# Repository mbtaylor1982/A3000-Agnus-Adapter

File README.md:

# A3000-Agnus-Adapter

## Intoduction
With the 8372B Agnus being a rare and expensive beast this adator was designed to allow the use of the relativly common 390544 (8375) 2MB Agnus from the A500+ and A600 in the A3000. 

## PAL or NTSC
Unlike the 8372B which can be changed between NTSC and PAL with a jumper, the 8375 (390544) can not. 

When selecting an Agnus chip to use with this adaptor there are two choices that have been tested:

1. 390544-01 PAL 2MB Agnus used in Eurpean A500+ and A600
2. 390544-02 NTSC 2MB Agnus Used in North American A500+ and A600

Other variants of the Agnus chip exist and provision has been made for then Vbb connection on pin 40 (C14M). 

If using one of the chips marked Vbb, C2 should be populated with a 0.1uF ceramic capacitor.

**Please note I have not tested any of the below chip revisions so the following info is provided as-is**

>318069-10
>Several pins have been changed to support the A600. This device supports PAL only - the PAL/_NTSC pad is internally pulled up to Vdd (+5). This part is the new rev of >what was previously called 390554-01, except that Vbb replaces the C14M pin.
>
>318069-11
>This pinout is identical to the -10. However, this device supports NTSC only - the PAL/_NTSC pad is internally connected to GND. This part is the new rev of what was >previously called 390554-02, except that Vbb replaces the C14M pin.
>
>318069-12
>Several pins have been changed to support the A600. This device supports PAL only - the PAL/_NTSC pad is internally pulled up to Vdd (+5). This part is the new rev of >what was previously called 390554-01.
>
>318069-13
>Several pins have been changed to support the A600. This device supports NTSC only - the PAL/_NTSC pad is internally connected to ground. This part is the new rev of >what was previously called 390554-02.

Source of above info > https://www.amigawiki.org/lib/exe/fetch.php?media=de:parts:agnus-history.pdf

## Components

| Component                                   | Location  | Qty | Link |
| ------------------------------------------- | --------- | --- | ---- |
| Ceramic Capacitor, 0.1uF, 0805              | C1, C2    | 2   |  [Mouser](https://www.mouser.com/ProductDetail/710-885012207098)    |
| 74AHC1G08 Single 2-Input AND Gate, SOT-23-5 | IC4       | 1   |  [Mouser](https://www.mouser.com/ProductDetail/595-SN74AHC1G08DBVR)    |
| PLCC 84 THT Socket                          |           | 1   | [Mouser](https://www.mouser.com/ProductDetail/3M-Electronic-Solutions-Division/8484-11B1-RK-TP?qs=WZRMhwwaLl9eNFJXLRGlFw==) |
|22-Pin, 2 Row Female header||4|[Mouser](https://www.mouser.se/ProductDetail/517-929975-01-11-RK)||
|22-Pin, 2 Row Male header||4|[Mouser](https://www.mouser.se/ProductDetail/649-77313-118-22LF)||

## Thanks
Thankyou to all the people who have helped with this project.

- Tristan Zondag for testing the adaptor (1st person to get it fully working)
- [Matt Harlum Liv2](https://github.com/LIV2) RAS signal combining inspired by the [A500-2Meg-Chip-ram](https://github.com/LIV2/A500-2Meg-Chip-ram) project.
- [John Chucky Hertell](https://github.com/ChuckyGang) & Peter Mulholland, initial conversations about the idea of using an A500+ Agnus.

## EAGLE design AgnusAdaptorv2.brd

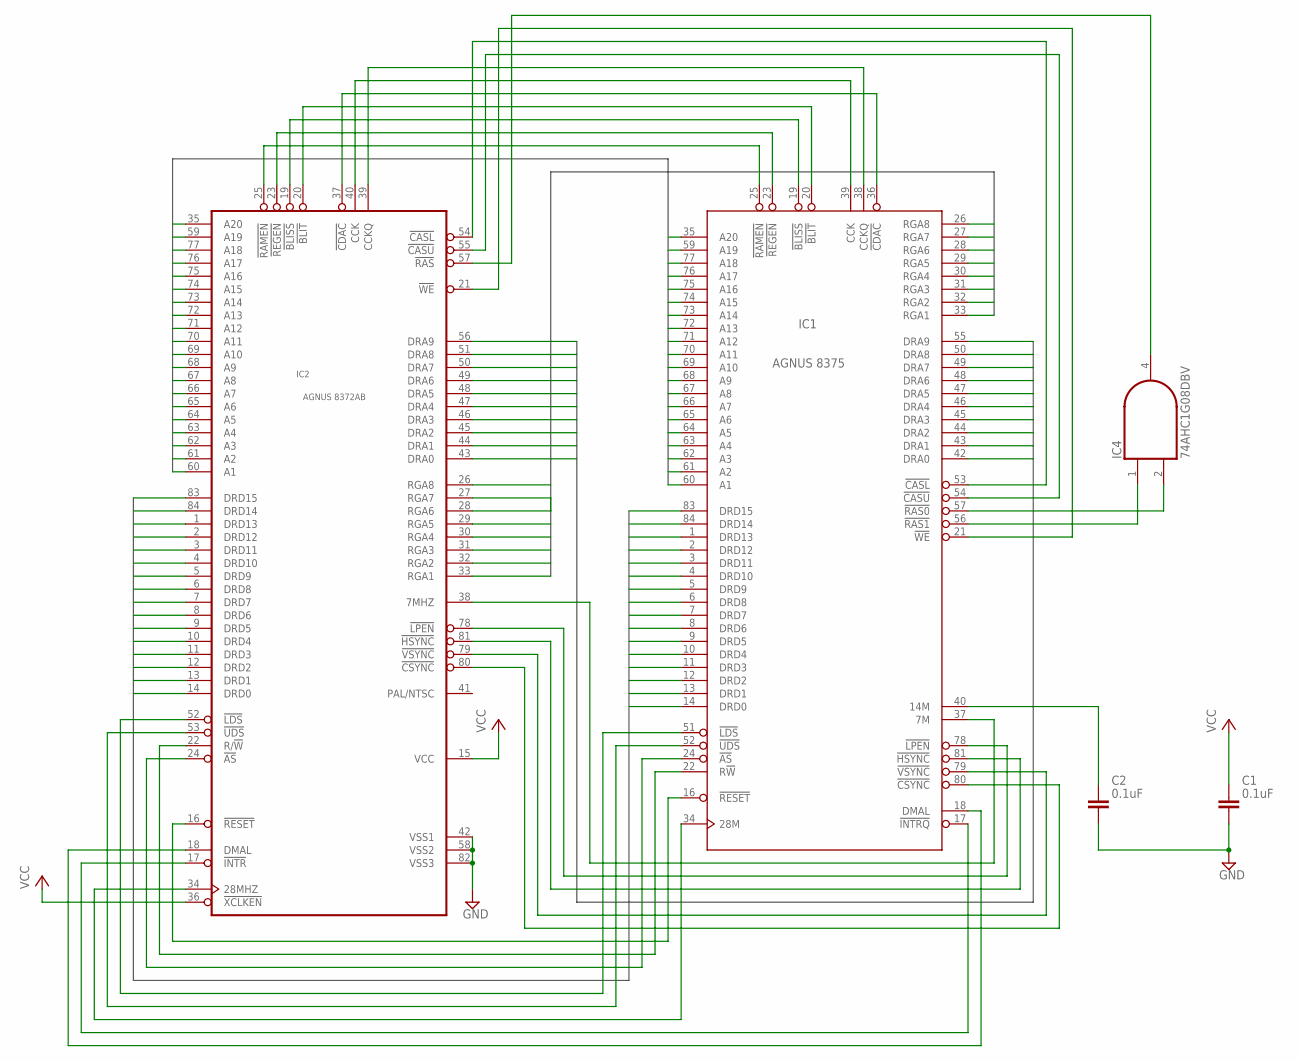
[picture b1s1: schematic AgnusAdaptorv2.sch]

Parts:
C1, C2: 0.1uF; CAPC2012X110
IC1: AGNUS_8375_A500+_A600_THT; PLCC84_T
IC2: A3000 Agnus Socket; PLCC84_T_H
IC4: 74AHC1G08DBV; SOT23-5

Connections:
7MHZ: IC1.37 (7M), IC2.38 (7MHZ)
28MHZ: IC1.34 (28M), IC2.34 (28MHZ)
!AS: IC1.24 (!AS), IC2.24 (!AS)
!BLISS: IC1.19 (!BLISS), IC2.19 (!BLISS)
!BLIT: IC1.20 (!BLIT), IC2.20 (!BLIT)
!CASL: IC1.53 (!CASL), IC2.54 (!CASL)
!CASU: IC1.54 (!CASU), IC2.55 (!CASU)
!CDAC: IC1.36 (!CDAC), IC2.37 (!CDAC)
!CSYNC: IC1.80 (!CSYNC), IC2.80 (!CSYNC)
!HSYNC: IC1.81 (!HSYNC), IC2.81 (!HSYNC)
!INTRQ: IC1.17 (!INTRQ), IC2.17 (!INTR)
!LDS: IC1.51 (!LDS), IC2.52 (!LDS)
!LPEN: IC1.78 (!LPEN), IC2.78 (!LPEN)
!RAMEN: IC1.25 (!RAMEN), IC2.25 (!RAMEN)
!RAS: IC2.57 (!RAS), IC4.4 (O)
!RAS0: IC1.57 (!RAS0), IC4.2 (I1)
!RAS1: IC1.56 (!RAS1), IC4.1 (I0)
!REGEN: IC1.23 (!REGEN), IC2.23 (!REGEN)
!RESET: IC1.16 (!RESET), IC2.16 (!RESET)
!UDS: IC1.52 (!UDS), IC2.53 (!UDS)
!VSYNC: IC1.79 (!VSYNC), IC2.79 (!VSYNC)
!WE: IC1.21 (!WE), IC2.21 (!WE)
A1: IC1.60 (A1), IC2.60 (A1)
A2: IC1.61 (A2), IC2.61 (A2)
A3: IC1.62 (A3), IC2.62 (A3)
A4: IC1.63 (A4), IC2.63 (A4)
A5: IC1.64 (A5), IC2.64 (A5)
A6: IC1.65 (A6), IC2.65 (A6)
A7: IC1.66 (A7), IC2.66 (A7)
A8: IC1.67 (A8), IC2.67 (A8)
A9: IC1.68 (A9), IC2.68 (A9)
A10: IC1.69 (A10), IC2.69 (A10)
A11: IC1.70 (A11), IC2.70 (A11)
A12: IC1.71 (A12), IC2.71 (A12)
A13: IC1.72 (A13), IC2.72 (A13)
A14: IC1.73 (A14), IC2.73 (A14)
A15: IC1.74 (A15), IC2.74 (A15)
A16: IC1.75 (A16), IC2.75 (A16)
A17: IC1.76 (A17), IC2.76 (A17)
A18: IC1.77 (A18), IC2.77 (A18)
A19: IC1.59 (A19), IC2.59 (A19)
A20: IC1.35 (A20), IC2.35 (A20)
CCK: IC1.39 (CCK), IC2.40 (CCK)
CCKQ: IC1.38 (CCKQ), IC2.39 (CCKQ)
DMAL: IC1.18 (DMAL), IC2.18 (DMAL)
DRA0: IC1.42 (DRA0), IC2.43 (DRA0)
DRA1: IC1.43 (DRA1), IC2.44 (DRA1)
DRA2: IC1.44 (DRA2), IC2.45 (DRA2)
DRA3: IC1.45 (DRA3), IC2.46 (DRA3)
DRA4: IC1.46 (DRA4), IC2.47 (DRA4)
DRA5: IC1.47 (DRA5), IC2.48 (DRA5)
DRA6: IC1.48 (DRA6), IC2.49 (DRA6)
DRA7: IC1.49 (DRA7), IC2.50 (DRA7)
DRA8: IC1.50 (DRA8), IC2.51 (DRA8)
DRA9: IC1.55 (DRA9), IC2.56 (DRA9)
DRD0: IC1.14 (DRD0), IC2.14 (DRD0)
DRD1: IC1.13 (DRD1), IC2.13 (DRD1)
DRD2: IC1.12 (DRD2), IC2.12 (DRD2)
DRD3: IC1.11 (DRD3), IC2.11 (DRD3)
DRD4: IC1.10 (DRD4), IC2.10 (DRD4)
DRD5: IC1.9 (DRD5), IC2.9 (DRD5)
DRD6: IC1.8 (DRD6), IC2.8 (DRD6)
DRD7: IC1.7 (DRD7), IC2.7 (DRD7)
DRD8: IC1.6 (DRD8), IC2.6 (DRD8)
DRD9: IC1.5 (DRD9), IC2.5 (DRD9)
DRD10: IC1.4 (DRD10), IC2.4 (DRD10)
DRD11: IC1.3 (DRD11), IC2.3 (DRD11)
DRD12: IC1.2 (DRD12), IC2.2 (DRD12)
DRD13: IC1.1 (DRD13), IC2.1 (DRD13)
DRD14: IC1.84 (DRD14), IC2.84 (DRD14)
DRD15: IC1.83 (DRD15), IC2.83 (DRD15)
GND: C1.2, C2.2, IC1.41 (GND), IC1.58 (GND), IC1.82 (GND), IC2.42 (VSS1), IC2.58 (VSS2), IC2.82 (VSS3), IC4.3 (GND)
unnamed: C2.1, IC1.40 (14M)
R!W: IC1.22 (R!W), IC2.22 (R/!W!)
RGA1: IC1.33 (RGA1), IC2.33 (RGA1)
RGA2: IC1.32 (RGA2), IC2.32 (RGA2)
RGA3: IC1.31 (RGA3), IC2.31 (RGA3)
RGA4: IC1.30 (RGA4), IC2.30 (RGA4)
RGA5: IC1.29 (RGA5), IC2.29 (RGA5)
RGA6: IC1.28 (RGA6), IC2.28 (RGA6)
RGA7: IC1.27 (RGA7), IC2.27 (RGA7)
RGA8: IC1.26 (RGA8), IC2.26 (RGA8)
VCC: C1.1, IC1.15 (VCC), IC2.15 (VCC), IC2.36 (!XCLKEN), IC4.5 (VCC)

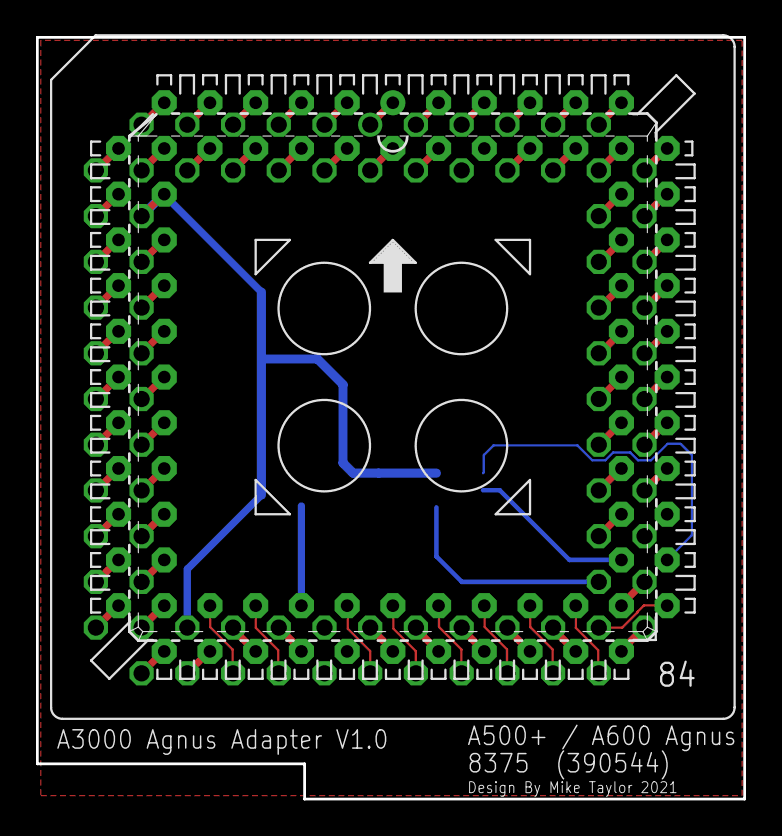
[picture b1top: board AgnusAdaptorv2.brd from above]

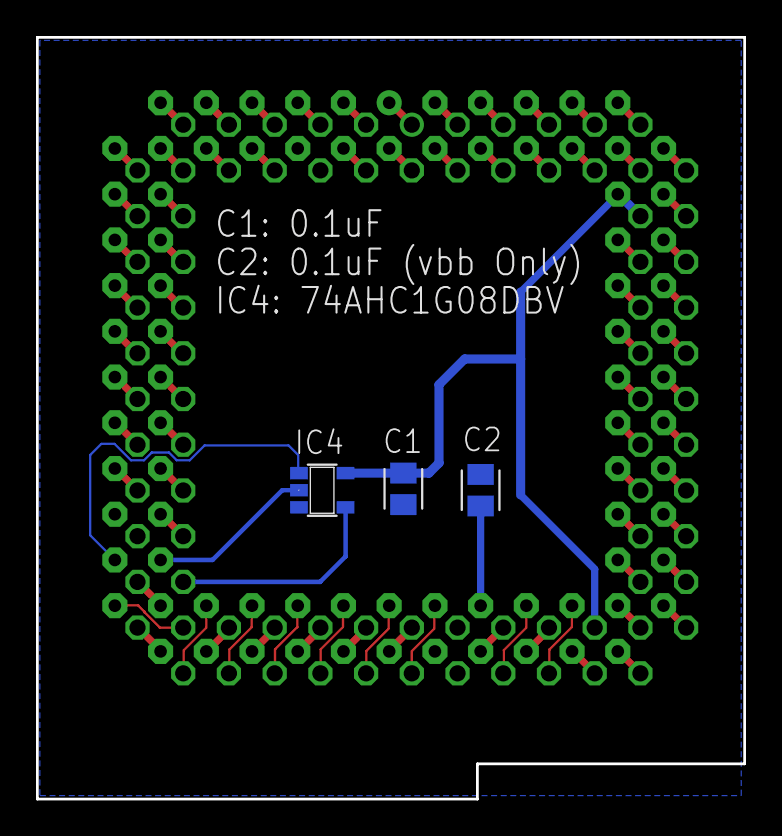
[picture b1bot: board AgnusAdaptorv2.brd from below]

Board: 2 copper layers, 39.3 x 42.3 mm, 5 parts (3 on the bottom side), 83 nets.

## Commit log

2020-12-04 Add files via upload
    Initial commit
2020-12-07 first go at routing complete
2020-12-07 fixed back annotation issue in board and added docs and libs
2021-09-29 Removed old files
2021-09-29 uploading tested first version
2021-09-29 Add images of adaptor
2021-09-30 Fixed some mistakes in README,md
2021-10-01 Add more pics and updated readme.md
2022-06-09 added PLCC 84 socket to Component list
2022-11-29 Update to Readme.md to add pin headers to the BOM
